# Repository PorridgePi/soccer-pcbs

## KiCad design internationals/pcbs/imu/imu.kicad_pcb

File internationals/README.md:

# PCBs for RoboCup 2024 Internationals
## Possible Improvements
- Establish proper design rules before starting the PCB design
    - Helps to avoid overlooking critical DRC errors (e.g. shorts) due to an abundance of minor errors (see TEMT8/GPIO14 in [bottom-rounded.kicad_pcb](https://github.com/PorridgePi/soccer-pcbs/blob/506bb3b5a68c0d0ed1313e4a490990bbbff14e21/internationals/pcbs/bottom/bottom-rounded.kicad_pcb) which shorted to ground thanks to a via intended to reduce EMI)
- Increase the general clearance (rather than the default 0.2mm)

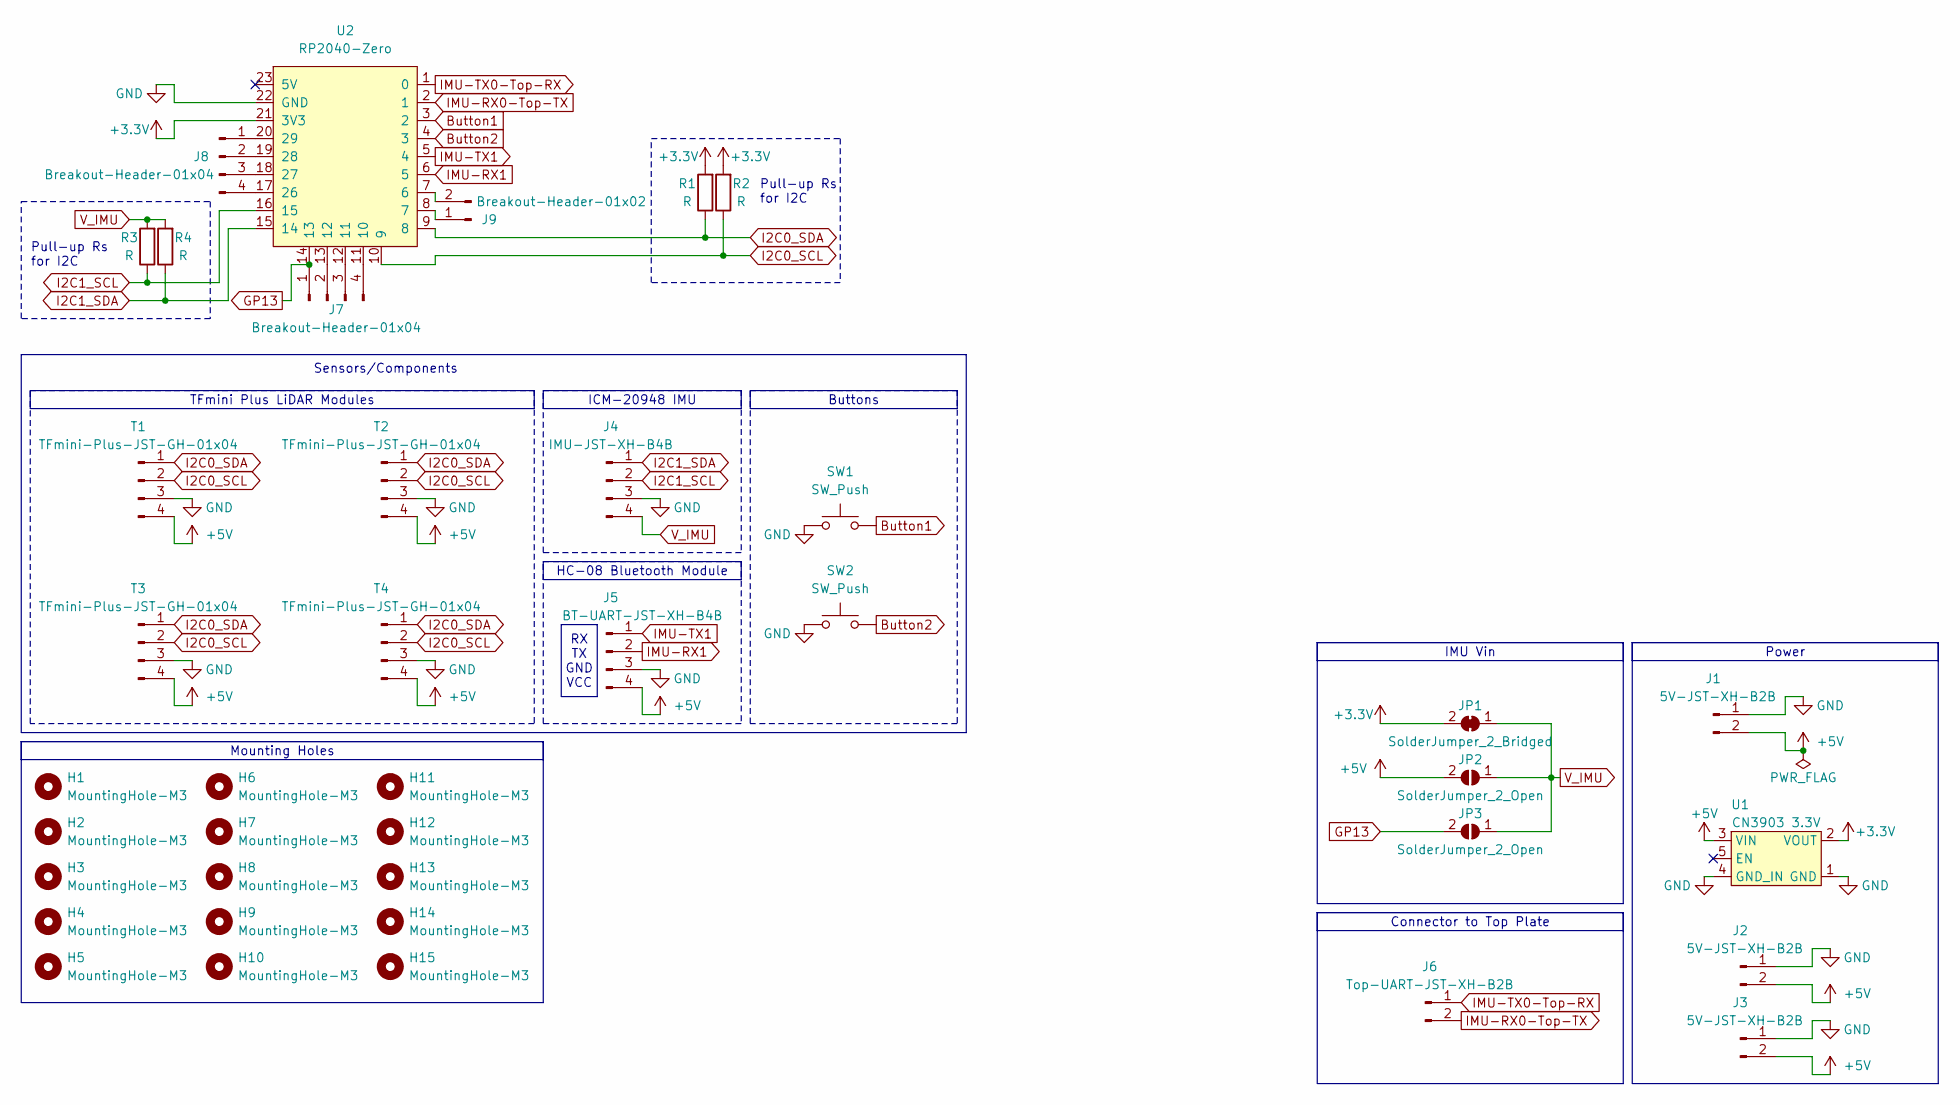
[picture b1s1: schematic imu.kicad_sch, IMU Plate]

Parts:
H1, H2, H3, H4, H5, H6, H7, H8, H9, H10, H11, H12, H13, H14, H15: MountingHole-M3; MountingHole_3.2mm_M3_Pad_Via
J1, J2, J3: 5V-JST-XH-B2B; JST_XH_B2B-XH-A_1x02_P2.50mm_Vertical
J4: IMU-JST-XH-B4B; JST_XH_B4B-XH-A_1x04_P2.50mm_Vertical
J5: BT-UART-JST-XH-B4B; JST_XH_B4B-XH-A_1x04_P2.50mm_Vertical
J6: Top-UART-JST-XH-B2B; JST_XH_B2B-XH-A_1x02_P2.50mm_Vertical
J7, J8: Breakout-Header-01x04; PinHeader_1x04_P2.54mm_Vertical
J9: Breakout-Header-01x02; PinHeader_1x02_P2.54mm_Vertical
JP1: SolderJumper_2_Bridged; SolderJumper-2_P1.3mm_Bridged_RoundedPad1.0x1.5mm
JP2, JP3: SolderJumper_2_Open; SolderJumper-2_P1.3mm_Open_RoundedPad1.0x1.5mm
R1, R2, R3, R4: R; R_Axial_DIN0204_L3.6mm_D1.6mm_P5.08mm_Horizontal
SW1, SW2: SW_Push; SW_PUSH_6mm
T1, T2, T3, T4: TFmini-Plus-JST-GH-01x04; JST_GH_BM04B-GHS-TBT_1x04-1MP_P1.25mm_Vertical
U1: CN3903 3.3V; CN3903
U2: RP2040-Zero

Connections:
+3.3V: JP1.2 (B), R1.2, R2.2, U1.2 (VOUT), U2.21 (3V3)
+5V: J1.2, J2.2, J3.2, J5.4, JP2.2 (B), T1.4, T2.4, T3.4, T4.4, U1.3 (VIN)
Button1: SW1.2, U2.3 (2)
Button2: SW2.2, U2.4 (3)
GND: J1.1, J2.1, J3.1, J4.3, J5.3, SW1.1, SW2.1, T1.3, T2.3, T3.3, T4.3, U1.1 (GND), U1.4 (GND_IN), U2.22 (GND)
GP13: J7.1, JP3.2 (B), U2.14 (13)
I2C0_SCL: R2.1, T1.2, T2.2, T3.2, T4.2, U2.10 (9)
I2C0_SDA: R1.1, T1.1, T2.1, T3.1, T4.1, U2.9 (8)
I2C1_SCL: J4.2, R3.1, U2.16 (15)
I2C1_SDA: J4.1, R4.1, U2.15 (14)
IMU-RX0-Top-TX: J6.2, U2.2 (1)
IMU-RX1: J5.2, U2.6 (5)
IMU-TX0-Top-RX: J6.1, U2.1 (0)
IMU-TX1: J5.1, U2.5 (4)
unnamed: J7.2, U2.13 (12)
unnamed: J7.3, U2.12 (11)
unnamed: J7.4, U2.11 (10)
unnamed: J8.1, U2.20 (29)
unnamed: J8.2, U2.19 (28)
unnamed: J8.3, U2.18 (27)
unnamed: J8.4, U2.17 (26)
unnamed: J9.1, U2.8 (7)
unnamed: J9.2, U2.7 (6)
V_IMU: J4.4, JP1.1 (A), JP2.1 (A), JP3.1 (A), R3.2, R4.2

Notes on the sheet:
Power
Connector to Top Plate
ICM-20948 IMU
Buttons
HC-08 Bluetooth Module
IMU Vin
RX TX GND VCC
Sensors/Components
TFmini Plus LiDAR Modules
Mounting Holes
Pull-up Rs for I2C

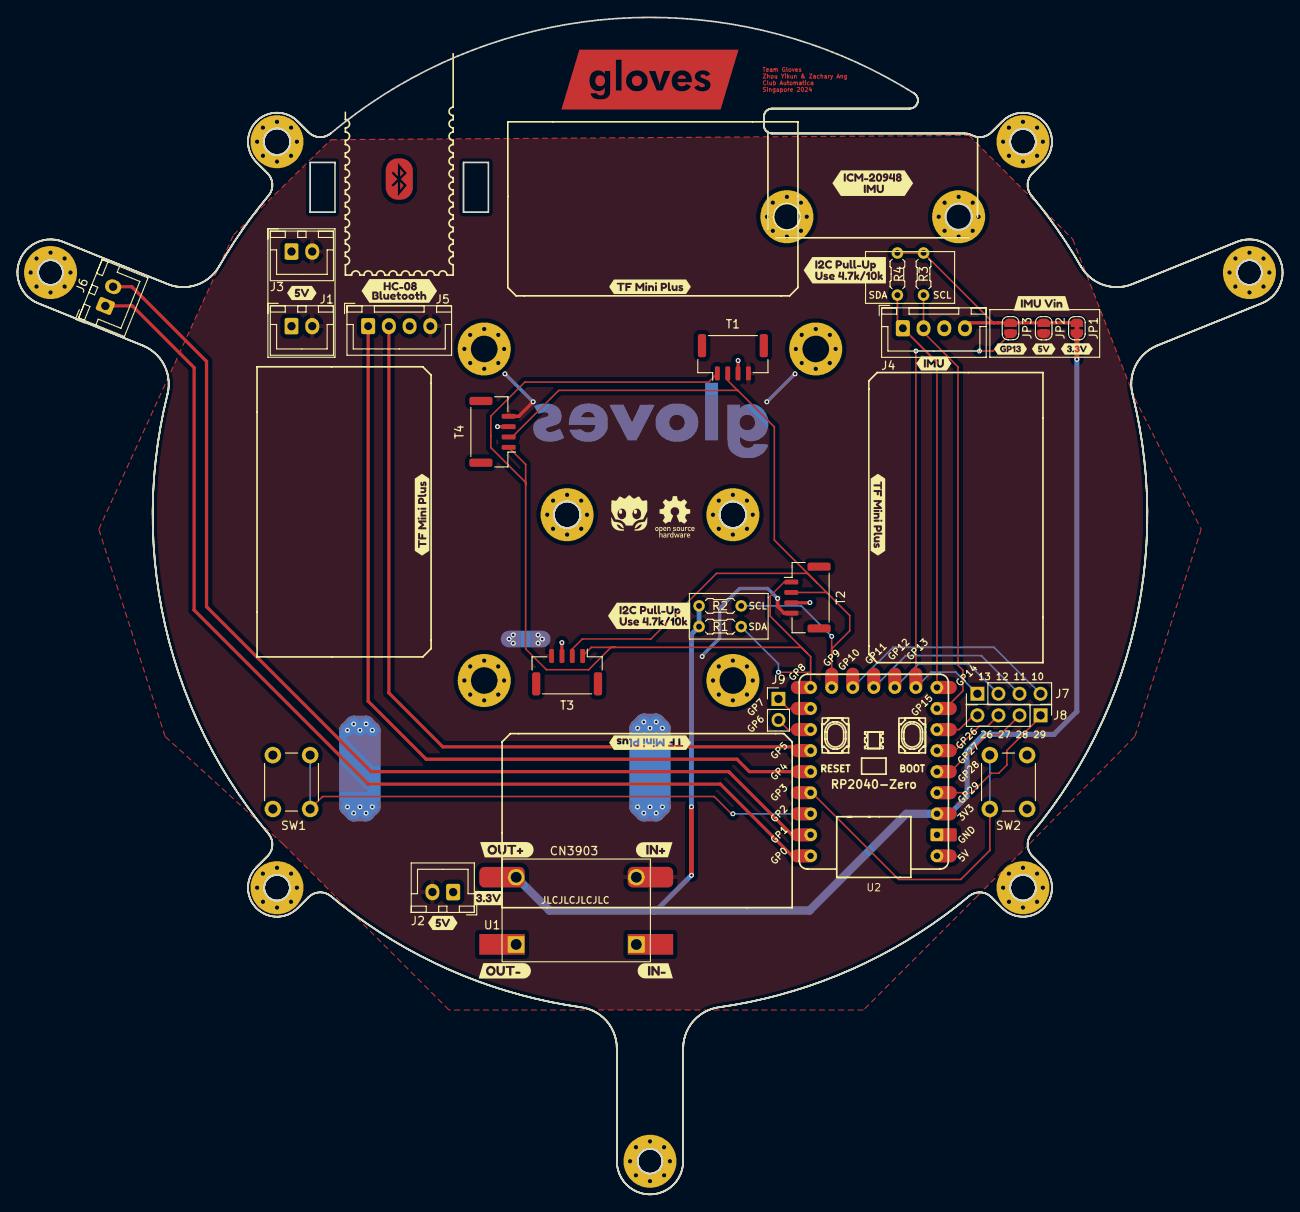
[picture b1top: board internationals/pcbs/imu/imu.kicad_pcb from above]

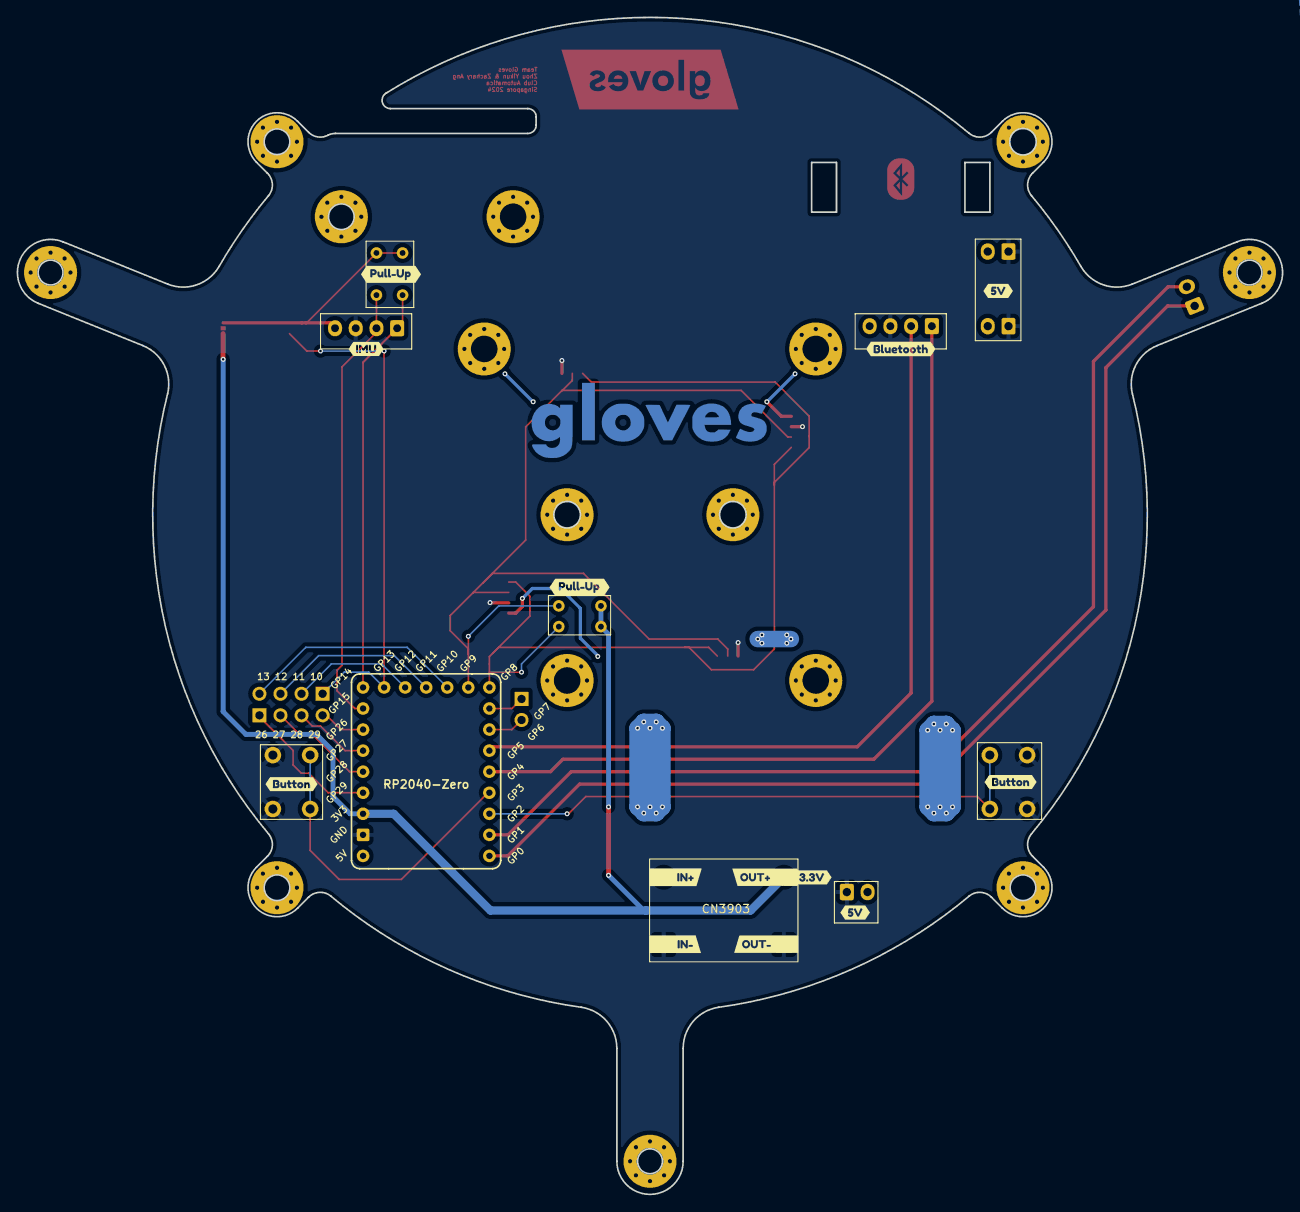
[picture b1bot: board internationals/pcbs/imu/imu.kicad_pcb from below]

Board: 2 copper layers, 152.6 x 142.0 mm, 66 parts (9 on the bottom side), 24 nets.

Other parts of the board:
kibuzzard-666B0E6A, kibuzzard-666B0E6A#2: G***; kibuzzard-666B0E6A
kibuzzard-66706AEF: G***; kibuzzard-66706AEF
kibuzzard-66706B28, kibuzzard-66706B28#2, kibuzzard-66706B28#3, kibuzzard-66706B28#4: G***; kibuzzard-66706B28
kibuzzard-66706BB5, kibuzzard-66706BB5#2, kibuzzard-66706BB5#3, kibuzzard-66706BB5#4: G***; kibuzzard-66706BB5
kibuzzard-667070EB: G***; kibuzzard-667070EB
kibuzzard-667070FD: G***; kibuzzard-667070FD
kibuzzard-667071A6: G***; kibuzzard-667071A6
kibuzzard-667073A4: G***; kibuzzard-667073A4
kibuzzard-667073EF, kibuzzard-667073EF#2: G***; kibuzzard-667073EF
kibuzzard-6670711B: G***; kibuzzard-6670711B
kibuzzard-6670727C: G***; kibuzzard-6670727C
kibuzzard-6670732F, kibuzzard-6670732F#2: G***; kibuzzard-6670732F
kibuzzard-6670735F: G***; kibuzzard-6670735F
kibuzzard-66707123: G***; kibuzzard-66707123
kibuzzard-66707133: G***; kibuzzard-66707133
kibuzzard-66707151: G***; kibuzzard-66707151
kibuzzard-66707423, kibuzzard-66707423#2: G***; kibuzzard-66707423

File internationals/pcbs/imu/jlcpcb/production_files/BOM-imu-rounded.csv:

Comment,Designator,Footprint,LCSC
5V-JST-XH-B2B,J2,JST_XH_B2B-XH-A_1x02_P2.50mm_Vertical,
CN3903 3.3V,U1,CN3903,
Breakout-Header-01x02,J9,PinHeader_1x02_P2.54mm_Vertical,
Breakout-Header-01x04,J7,PinHeader_1x04_P2.54mm_Vertical,
TFmini-Plus-JST-GH-01x04,T4,JST_GH_BM04B-GHS-TBT_1x04-1MP_P1.25mm_Vertical,
SolderJumper_2_Bridged,JP1,SolderJumper-2_P1.3mm_Bridged_RoundedPad1.0x1.5mm,
Top-UART-JST-XH-B2B,J6,JST_XH_B2B-XH-A_1x02_P2.50mm_Vertical,
SolderJumper_2_Open,JP2,SolderJumper-2_P1.3mm_Open_RoundedPad1.0x1.5mm,
R,R4,R_Axial_DIN0204_L3.6mm_D1.6mm_P5.08mm_Horizontal,
R,R1,R_Axial_DIN0204_L3.6mm_D1.6mm_P5.08mm_Horizontal,
TFmini-Plus-JST-GH-01x04,T3,JST_GH_BM04B-GHS-TBT_1x04-1MP_P1.25mm_Vertical,
TFmini-Plus-JST-GH-01x04,T2,JST_GH_BM04B-GHS-TBT_1x04-1MP_P1.25mm_Vertical,
SolderJumper_2_Open,JP3,SolderJumper-2_P1.3mm_Open_RoundedPad1.0x1.5mm,
BT-UART-JST-XH-B4B,J5,JST_XH_B4B-XH-A_1x04_P2.50mm_Vertical,
TFmini-Plus-JST-GH-01x04,T1,JST_GH_BM04B-GHS-TBT_1x04-1MP_P1.25mm_Vertical,
5V-JST-XH-B2B,J1,JST_XH_B2B-XH-A_1x02_P2.50mm_Vertical,
Breakout-Header-01x04,J8,PinHeader_1x04_P2.54mm_Vertical,
SW_Push,SW1,SW_PUSH_6mm,
R,R3,R_Axial_DIN0204_L3.6mm_D1.6mm_P5.08mm_Horizontal,
RP2040-Zero,U2,RP2040-Zero,
R,R2,R_Axial_DIN0204_L3.6mm_D1.6mm_P5.08mm_Horizontal,
IMU-JST-XH-B4B,J4,JST_XH_B4B-XH-A_1x04_P2.50mm_Vertical,
SW_Push,SW2,SW_PUSH_6mm,
5V-JST-XH-B2B,J3,JST_XH_B2B-XH-A_1x02_P2.50mm_Vertical,

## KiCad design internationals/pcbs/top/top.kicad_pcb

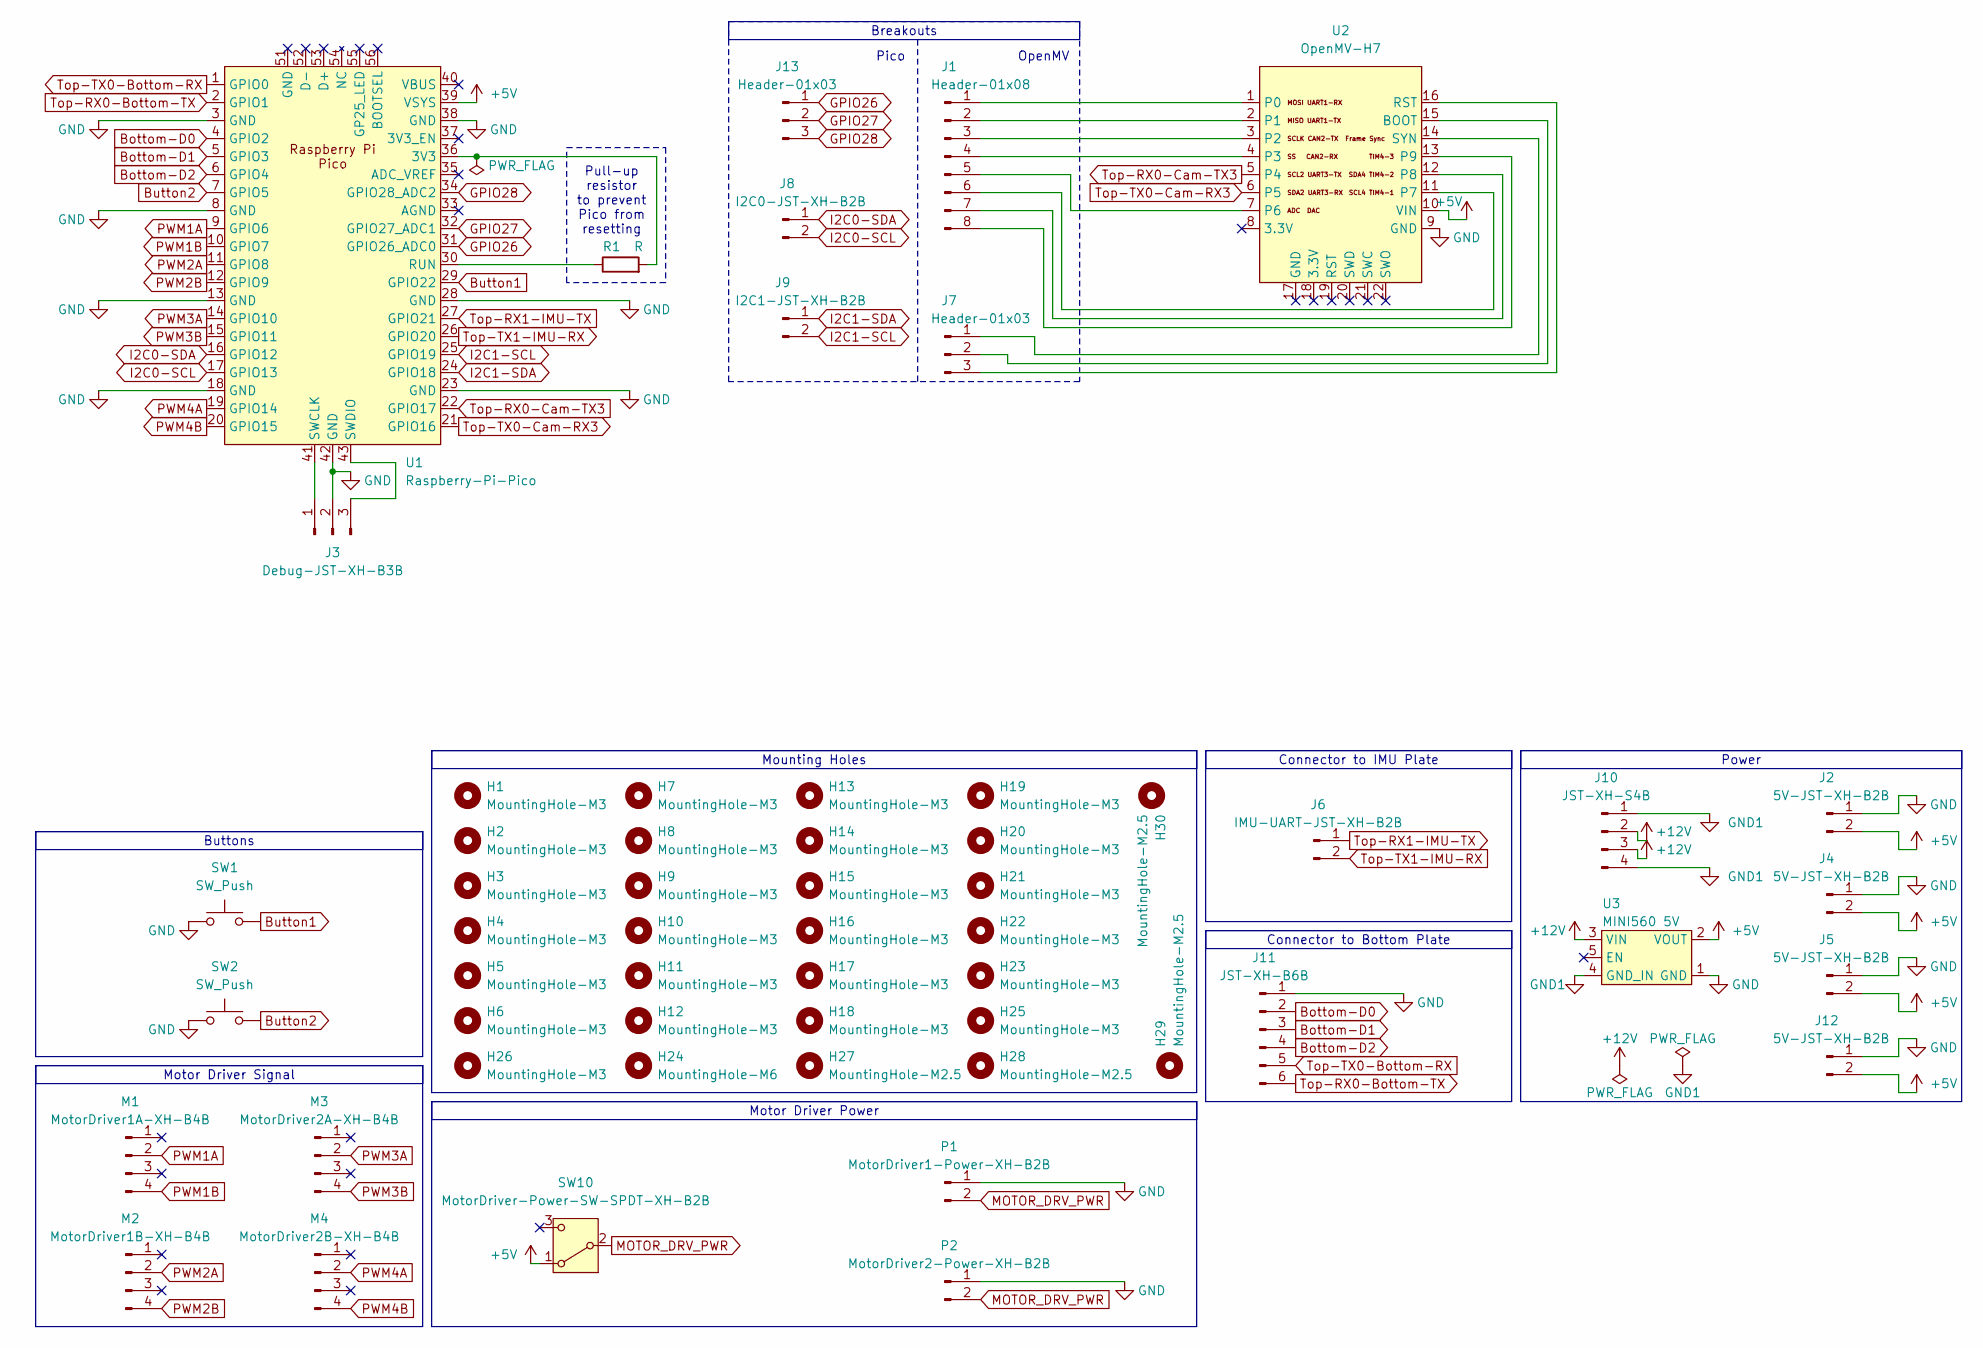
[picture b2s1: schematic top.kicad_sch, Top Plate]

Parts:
H1, H2, H3, H4, H5, H6, H7, H8, H9, H10, H11, H12, H13, H14, H15, H16, H17, H18, H19, H20, H21, H22, H23, H25, H26: MountingHole-M3; MountingHole_3.2mm_M3_Pad_Via
H24: MountingHole-M6; MountingHole_6.4mm_M6_Pad_Via
H27, H28, H29, H30: MountingHole-M2.5; MountingHole_2.7mm_M2.5_Pad_Via
J1: Header-01x08; PinHeader_1x08_P2.54mm_Vertical
J2, J4, J5, J12: 5V-JST-XH-B2B; JST_XH_B2B-XH-A_1x02_P2.50mm_Vertical
J3: Debug-JST-XH-B3B; JST_XH_B3B-XH-A_1x03_P2.50mm_Vertical
J6: IMU-UART-JST-XH-B2B; JST_XH_B2B-XH-A_1x02_P2.50mm_Vertical
J7, J13: Header-01x03; PinHeader_1x03_P2.54mm_Vertical
J8: I2C0-JST-XH-B2B; JST_XH_B2B-XH-A_1x02_P2.50mm_Vertical
J9: I2C1-JST-XH-B2B; JST_XH_B2B-XH-A_1x02_P2.50mm_Vertical
J10: JST-XH-S4B; JST_XH_S4B-XH-A_1x04_P2.50mm_Horizontal
J11: JST-XH-B6B; JST_XH_B6B-XH-A_1x06_P2.50mm_Vertical
M1: MotorDriver1A-XH-B4B; JST_XH_B4B-XH-A_1x04_P2.50mm_Vertical
M2: MotorDriver1B-XH-B4B; JST_XH_B4B-XH-A_1x04_P2.50mm_Vertical
M3: MotorDriver2A-XH-B4B; JST_XH_B4B-XH-A_1x04_P2.50mm_Vertical
M4: MotorDriver2B-XH-B4B; JST_XH_B4B-XH-A_1x04_P2.50mm_Vertical
P1: MotorDriver1-Power-XH-B2B; JST_XH_B2B-XH-A_1x02_P2.50mm_Vertical
P2: MotorDriver2-Power-XH-B2B; JST_XH_B2B-XH-A_1x02_P2.50mm_Vertical
R1: R; R_Axial_DIN0204_L3.6mm_D1.6mm_P5.08mm_Horizontal
SW1, SW2: SW_Push; SW_PUSH_6mm
SW10: MotorDriver-Power-SW-SPDT-XH-B2B; JST_XH_B2B-XH-A_1x02_P2.50mm_Vertical
U1: Raspberry-Pi-Pico
U2: OpenMV-H7
U3: MINI560 5V; MINI560

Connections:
+5V: J2.2, J4.2, J5.2, J12.2, SW10.1 (A), U1.39 (VSYS), U2.10 (VIN), U3.2 (VOUT)
+12V: J10.2, J10.3, U3.3 (VIN)
Bottom-D0: J11.2, U1.4 (GPIO2)
Bottom-D1: J11.3, U1.5 (GPIO3)
Bottom-D2: J11.4, U1.6 (GPIO4)
Button1: SW1.2, U1.29 (GPIO22)
Button2: SW2.2, U1.7 (GPIO5)
GND: J2.1, J3.2, J4.1, J5.1, J11.1, J12.1, P1.1, P2.1, SW1.1, SW2.1, U1.3 (GND), U1.8 (GND), U1.13 (GND), U1.18 (GND), U1.23 (GND), U1.28 (GND), U1.38 (GND), U1.42 (GND), U2.9 (GND), U3.1 (GND)
GND1: J10.1, J10.4, U3.4 (GND_IN)
GPIO26: J13.1, U1.31 (GPIO26_ADC0)
GPIO27: J13.2, U1.32 (GPIO27_ADC1)
GPIO28: J13.3, U1.34 (GPIO28_ADC2)
I2C0-SCL: J8.2, U1.17 (GPIO13)
I2C0-SDA: J8.1, U1.16 (GPIO12)
I2C1-SCL: J9.2, U1.25 (GPIO19)
I2C1-SDA: J9.1, U1.24 (GPIO18)
MOTOR_DRV_PWR: P1.2, P2.2, SW10.2 (B)
unnamed: J1.1, U2.1 (P0)
unnamed: J1.2, U2.2 (P1)
unnamed: J1.3, U2.3 (P2)
unnamed: J1.4, U2.4 (P3)
unnamed: J1.5, U2.7 (P6)
unnamed: J1.6, U2.11 (P7)
unnamed: J1.7, U2.12 (P8)
unnamed: J1.8, U2.13 (P9)
unnamed: J3.1, U1.41 (SWCLK)
unnamed: J3.3, U1.43 (SWDIO)
unnamed: J7.1, U2.14 (SYN)
unnamed: J7.2, U2.15 (BOOT)
unnamed: J7.3, U2.16 (RST)
unnamed: R1.2, U1.36 (3V3)
unnamed: R1.1, U1.30 (RUN)
PWM1A: M1.2, U1.9 (GPIO6)
PWM1B: M1.4, U1.10 (GPIO7)
PWM2A: M2.2, U1.11 (GPIO8)
PWM2B: M2.4, U1.12 (GPIO9)
PWM3A: M3.2, U1.14 (GPIO10)
PWM3B: M3.4, U1.15 (GPIO11)
PWM4A: M4.2, U1.19 (GPIO14)
PWM4B: M4.4, U1.20 (GPIO15)
Top-RX0-Bottom-TX: J11.6, U1.2 (GPIO1)
Top-RX0-Cam-TX3: U1.22 (GPIO17), U2.5 (P4)
Top-RX1-IMU-TX: J6.1, U1.27 (GPIO21)
Top-TX0-Bottom-RX: J11.5, U1.1 (GPIO0)
Top-TX0-Cam-RX3: U1.21 (GPIO16), U2.6 (P5)
Top-TX1-IMU-RX: J6.2, U1.26 (GPIO20)

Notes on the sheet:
Buttons
Motor Driver Power
Motor Driver Signal
Connector to IMU Plate
Power
Breakouts
Mounting Holes
Connector to Bottom Plate
Pull-up resistor to prevent Pico from resetting
Pico
OpenMV

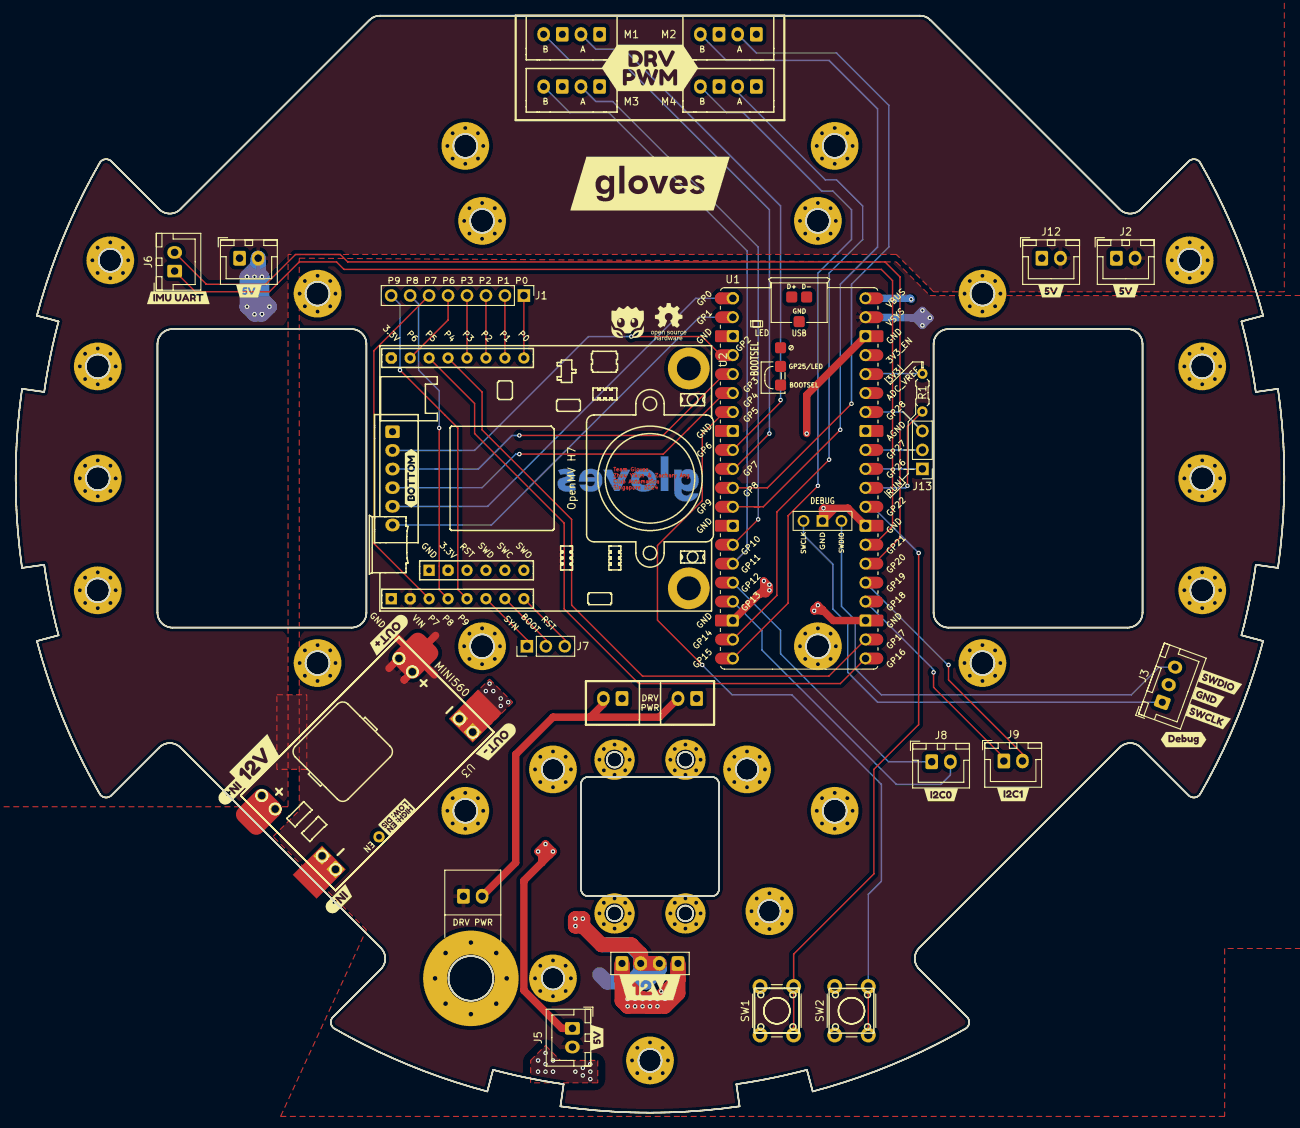
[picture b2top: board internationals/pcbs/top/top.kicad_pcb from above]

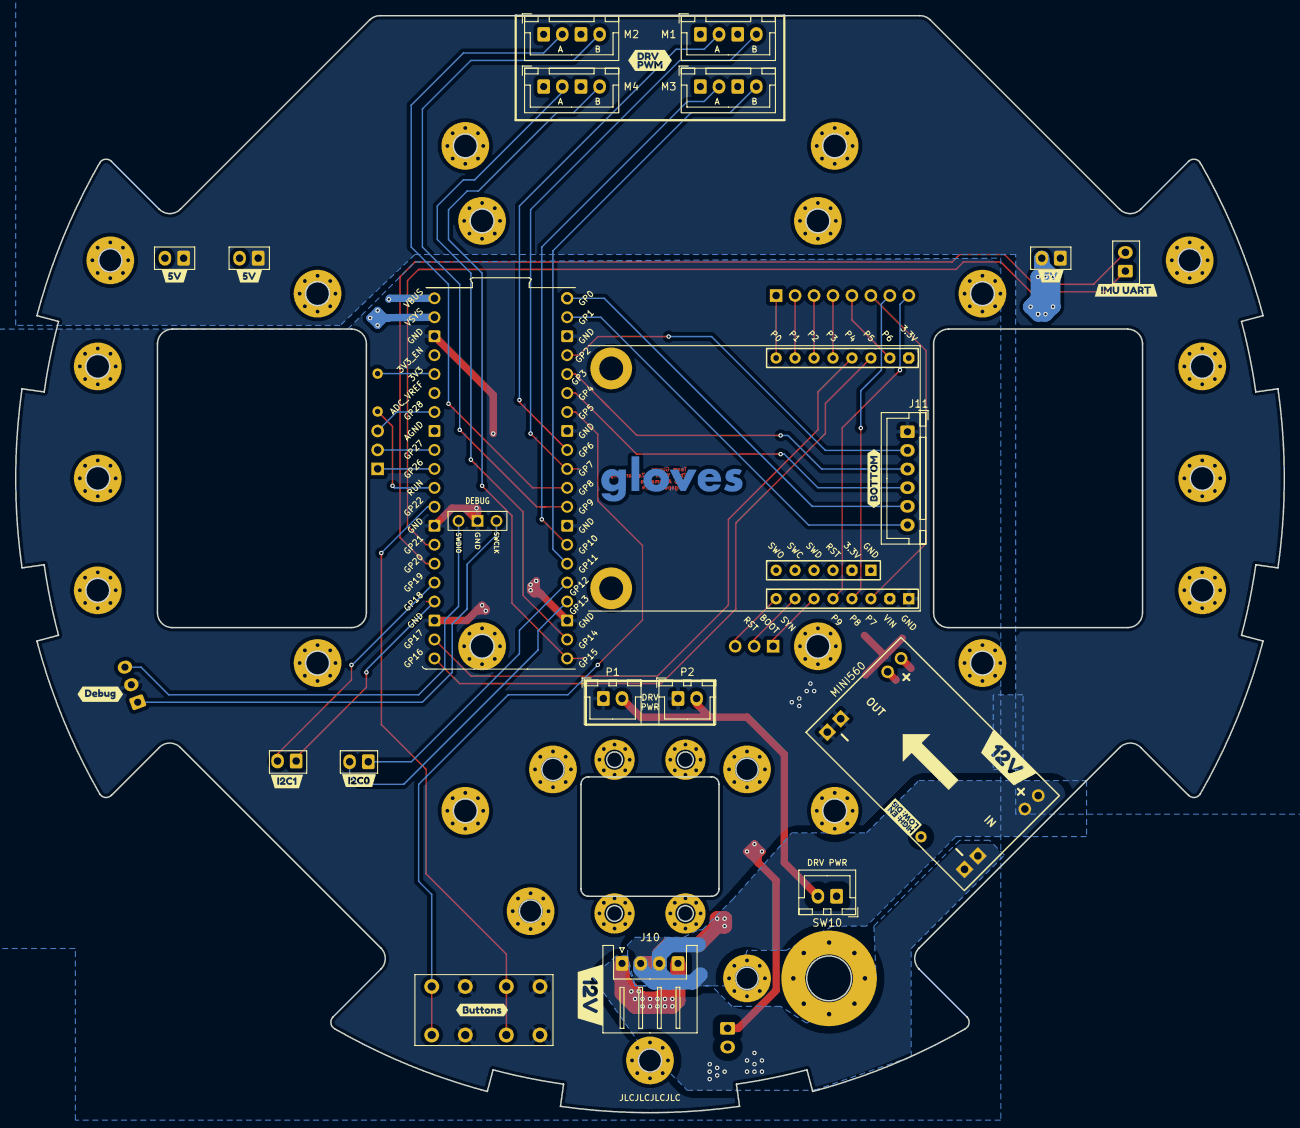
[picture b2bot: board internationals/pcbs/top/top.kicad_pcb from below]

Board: 2 copper layers, 170.0 x 147.0 mm, 84 parts (21 on the bottom side), 46 nets.

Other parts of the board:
kibuzzard-666B0E6A: G***; kibuzzard-666B0E6A
kibuzzard-666D6A28, kibuzzard-666D6A28#2, kibuzzard-666D6A28#3, kibuzzard-666D6A28#4, kibuzzard-666D6A28#5, kibuzzard-666D6A28#6, kibuzzard-666D6A28#7: G***; kibuzzard-666D6A28
kibuzzard-666D6AFC, kibuzzard-666D6AFC#2, kibuzzard-666D6AFC#3: G***; kibuzzard-666D6AFC
kibuzzard-666D6B3A: G***; kibuzzard-666D6B3A
kibuzzard-666D6C3F, kibuzzard-666D6C3F#2: G***; kibuzzard-666D6C3F
kibuzzard-666D6C08, kibuzzard-666D6C08#2: G***; kibuzzard-666D6C08
kibuzzard-666D6C77: G***; kibuzzard-666D6C77
kibuzzard-666D6C83: G***; kibuzzard-666D6C83
kibuzzard-666D6C87: G***; kibuzzard-666D6C87
kibuzzard-666D6D8F, kibuzzard-666D6D8F#2: G***; kibuzzard-666D6D8F
kibuzzard-666D6EB8: G***; kibuzzard-666D6EB8
kibuzzard-666D6EEA: G***; kibuzzard-666D6EEA
kibuzzard-666D6FA1, kibuzzard-666D6FA1#2: G***; kibuzzard-666D6FA1
kibuzzard-666D7734, kibuzzard-666D7734#2: G***; kibuzzard-666D7734
kibuzzard-666D7803: G***; kibuzzard-666D7803

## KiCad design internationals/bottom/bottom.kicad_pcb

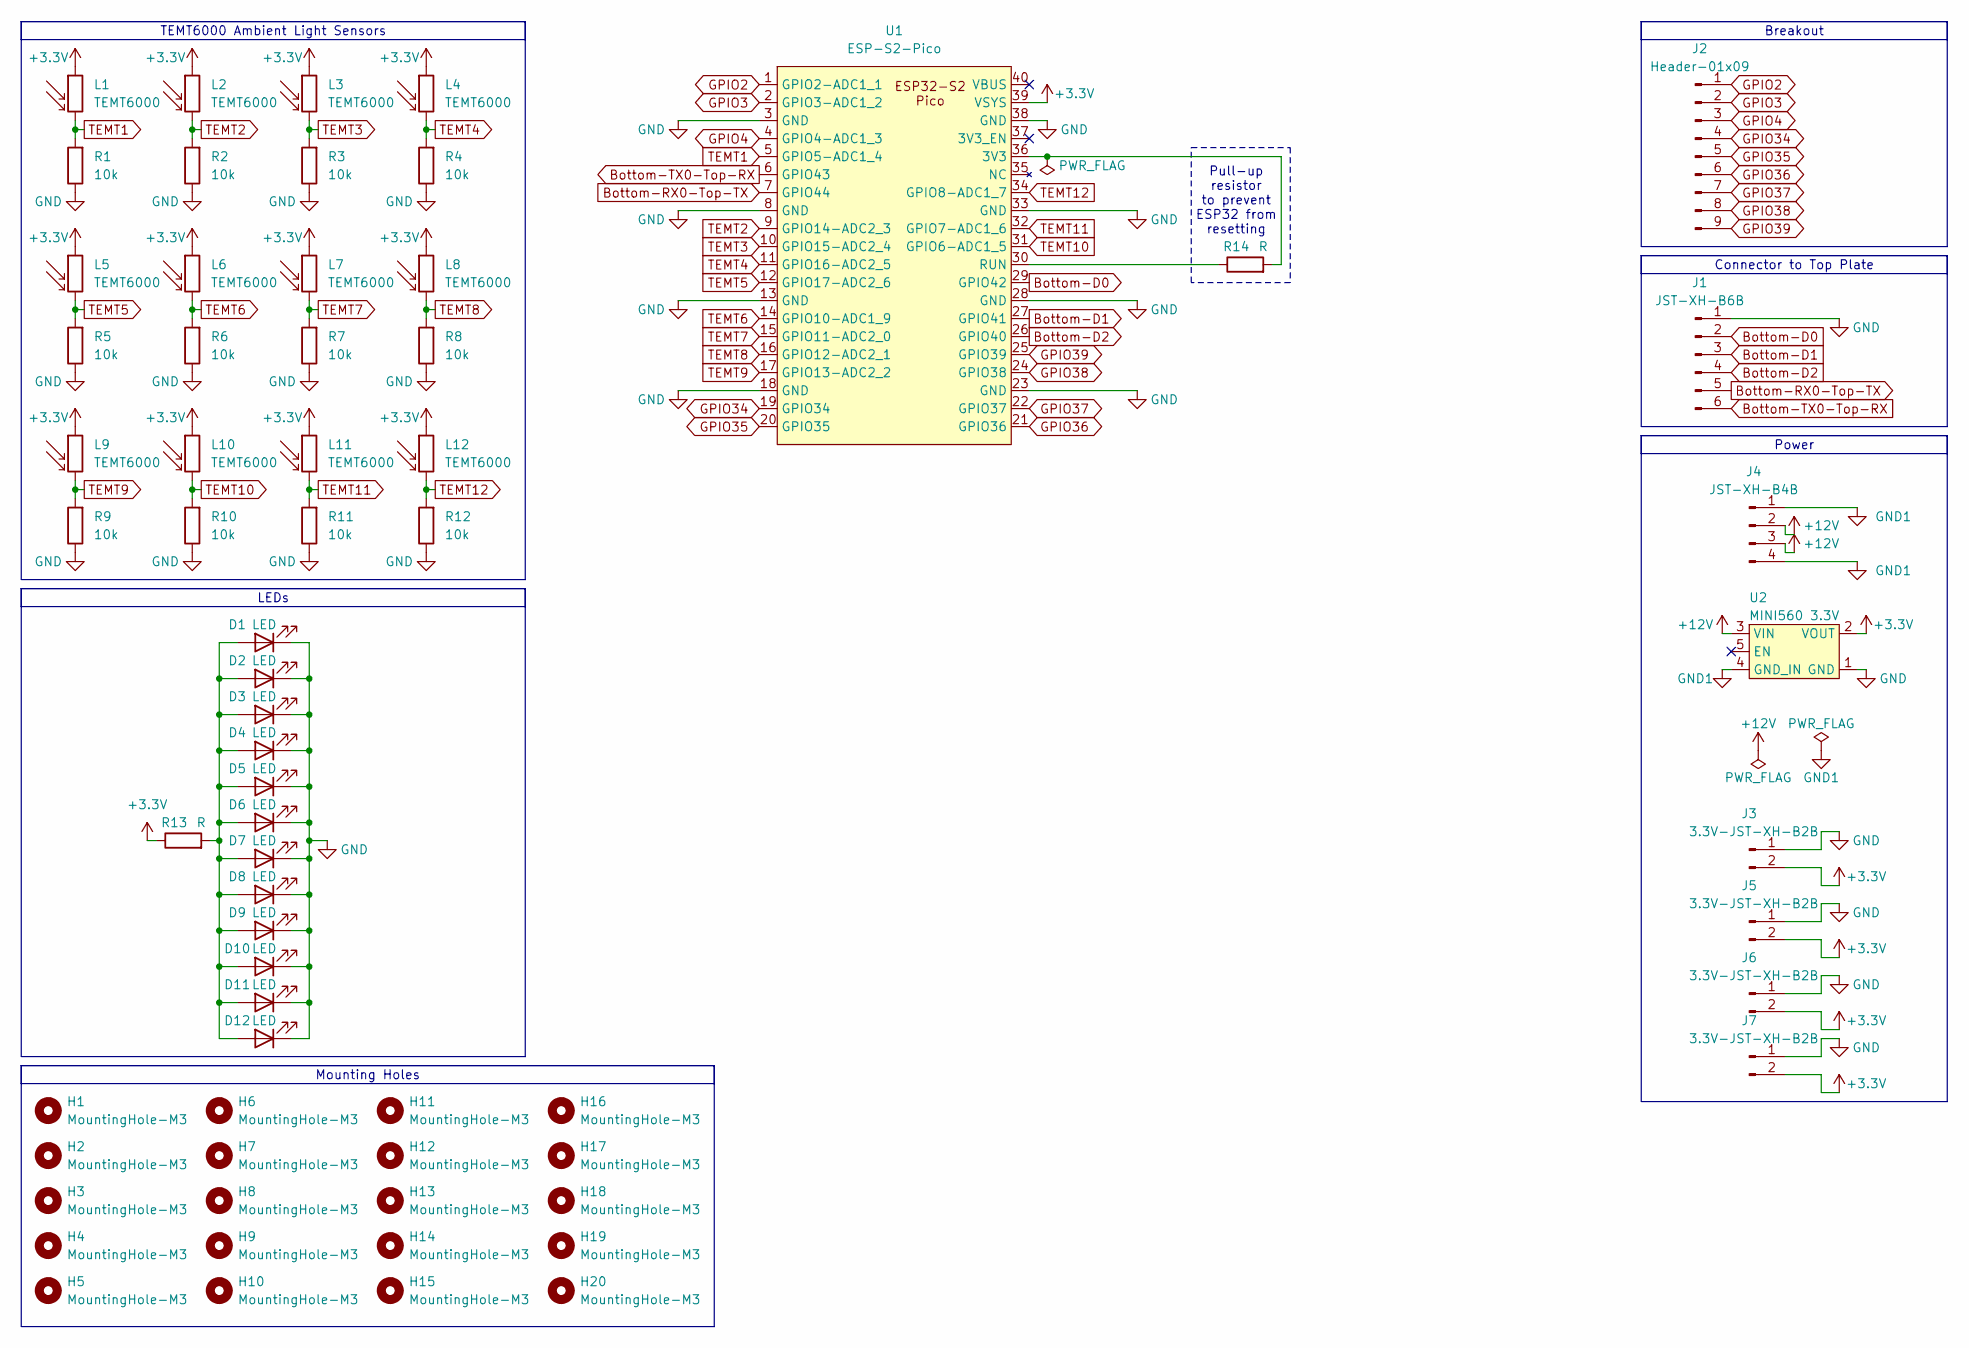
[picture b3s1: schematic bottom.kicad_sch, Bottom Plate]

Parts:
D1, D2, D3, D4, D5, D6, D7, D8, D9, D10, D11, D12: LED; LED-6028-SMD
H1, H2, H3, H4, H5, H6, H7, H8, H9, H10, H11, H12, H13, H14, H15, H16, H17, H18, H19, H20: MountingHole-M3; MountingHole_3.2mm_M3_Pad_Via
J1: JST-XH-B6B; JST_XH_B6B-XH-A_1x06_P2.50mm_Vertical
J2: Header-01x09; PinHeader_1x09_P2.54mm_Vertical
J3, J5, J6, J7: 3.3V-JST-XH-B2B; JST_XH_B2B-XH-A_1x02_P2.50mm_Vertical
J4: JST-XH-B4B; JST_XH_B4B-XH-A_1x04_P2.50mm_Vertical
L1, L2, L3, L4, L5, L6, L7, L8, L9, L10, L11, L12: TEMT6000; TEMT6000-SMD
R1, R2, R3, R4, R5, R6, R7, R8, R9, R10, R11, R12: 10k; R_0603_1608Metric_Pad0.98x0.95mm_HandSolder
R13, R14: R; R_Axial_DIN0204_L3.6mm_D1.6mm_P5.08mm_Horizontal
U1: ESP-S2-Pico; ESP32-S2-Pico
U2: MINI560 3.3V; MINI560

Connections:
+3.3V: J3.2, J5.2, J6.2, J7.2, L1.1, L2.1, L3.1, L4.1, L5.1, L6.1, L7.1, L8.1, L9.1, L10.1, L11.1, L12.1, R13.1, U1.39 (VSYS), U2.2 (VOUT)
+12V: J4.2, J4.3, U2.3 (VIN)
Bottom-D0: J1.2, U1.29 (GPIO42)
Bottom-D1: J1.3, U1.27 (GPIO41)
Bottom-D2: J1.4, U1.26 (GPIO40)
Bottom-RX0-Top-TX: J1.5, U1.7 (GPIO44)
Bottom-TX0-Top-RX: J1.6, U1.6 (GPIO43)
GND: D1.1 (K), D2.1 (K), D3.1 (K), D4.1 (K), D5.1 (K), D6.1 (K), D7.1 (K), D8.1 (K), D9.1 (K), D10.1 (K), D11.1 (K), D12.1 (K), J1.1, J3.1, J5.1, J6.1, J7.1, R1.1, R2.1, R3.1, R4.1, R5.1, R6.1, R7.1, R8.1, R9.1, R10.1, R11.1, R12.1, U1.3 (GND), U1.8 (GND), U1.13 (GND), U1.18 (GND), U1.23 (GND), U1.28 (GND), U1.33 (GND), U1.38 (GND), U2.1 (GND)
GND1: J4.1, J4.4, U2.4 (GND_IN)
GPIO2: J2.1, U1.1 (GPIO2-ADC1_1)
GPIO3: J2.2, U1.2 (GPIO3-ADC1_2)
GPIO4: J2.3, U1.4 (GPIO4-ADC1_3)
GPIO34: J2.4, U1.19 (GPIO34)
GPIO35: J2.5, U1.20 (GPIO35)
GPIO36: J2.6, U1.21 (GPIO36)
GPIO37: J2.7, U1.22 (GPIO37)
GPIO38: J2.8, U1.24 (GPIO38)
GPIO39: J2.9, U1.25 (GPIO39)
unnamed: D1.2 (A), D2.2 (A), D3.2 (A), D4.2 (A), D5.2 (A), D6.2 (A), D7.2 (A), D8.2 (A), D9.2 (A), D10.2 (A), D11.2 (A), D12.2 (A), R13.2
unnamed: R14.2, U1.36 (3V3)
unnamed: R14.1, U1.30 (RUN)
TEMT1: L1.2, R1.2, U1.5 (GPIO5-ADC1_4)
TEMT2: L2.2, R2.2, U1.9 (GPIO14-ADC2_3)
TEMT3: L3.2, R3.2, U1.10 (GPIO15-ADC2_4)
TEMT4: L4.2, R4.2, U1.11 (GPIO16-ADC2_5)
TEMT5: L5.2, R5.2, U1.12 (GPIO17-ADC2_6)
TEMT6: L6.2, R6.2, U1.14 (GPIO10-ADC1_9)
TEMT7: L7.2, R7.2, U1.15 (GPIO11-ADC2_0)
TEMT8: L8.2, R8.2, U1.16 (GPIO12-ADC2_1)
TEMT9: L9.2, R9.2, U1.17 (GPIO13-ADC2_2)
TEMT10: L10.2, R10.2, U1.31 (GPIO6-ADC1_5)
TEMT11: L11.2, R11.2, U1.32 (GPIO7-ADC1_6)
TEMT12: L12.2, R12.2, U1.34 (GPIO8-ADC1_7)

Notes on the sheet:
Breakout
LEDs
Connector to Top Plate
Mounting Holes
Power
TEMT6000 Ambient Light Sensors
Pull-up resistor to prevent ESP32 from resetting

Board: 2 copper layers, 84 parts (29 on the bottom side), 33 nets, no tracks yet.

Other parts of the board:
kibuzzard-6669C5DE: G***; kibuzzard-6669C5DE
kibuzzard-6669C5ED, kibuzzard-6669C5ED#2, kibuzzard-6669C5ED#3, kibuzzard-6669C5ED#4: G***; kibuzzard-6669C5ED
kibuzzard-6669C6B5: G***; kibuzzard-6669C6B5
kibuzzard-6669C6DE: G***; kibuzzard-6669C6DE
kibuzzard-6669C6E8: G***; kibuzzard-6669C6E8
kibuzzard-6669C6EF: G***; kibuzzard-6669C6EF
kibuzzard-6669C9E8: G***; kibuzzard-6669C9E8
kibuzzard-6669C688: G***; kibuzzard-6669C688
kibuzzard-6669C702: G***; kibuzzard-6669C702
kibuzzard-6669C706: G***; kibuzzard-6669C706
kibuzzard-6669C956, kibuzzard-6669C956#2, kibuzzard-6669C956#3, kibuzzard-6669C956#4: G***; kibuzzard-6669C956
